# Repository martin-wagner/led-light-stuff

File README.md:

# led-light-stuff

various stuff to make led light
- circuit diagrams
- pcb images
- bom (not shure how accurate they are)
- image of hardware prototype

driver pins 2,3,4,5 - 9,10,11,12 - 17,18,19,20 do select microcontroller output color. solder only the one you want.

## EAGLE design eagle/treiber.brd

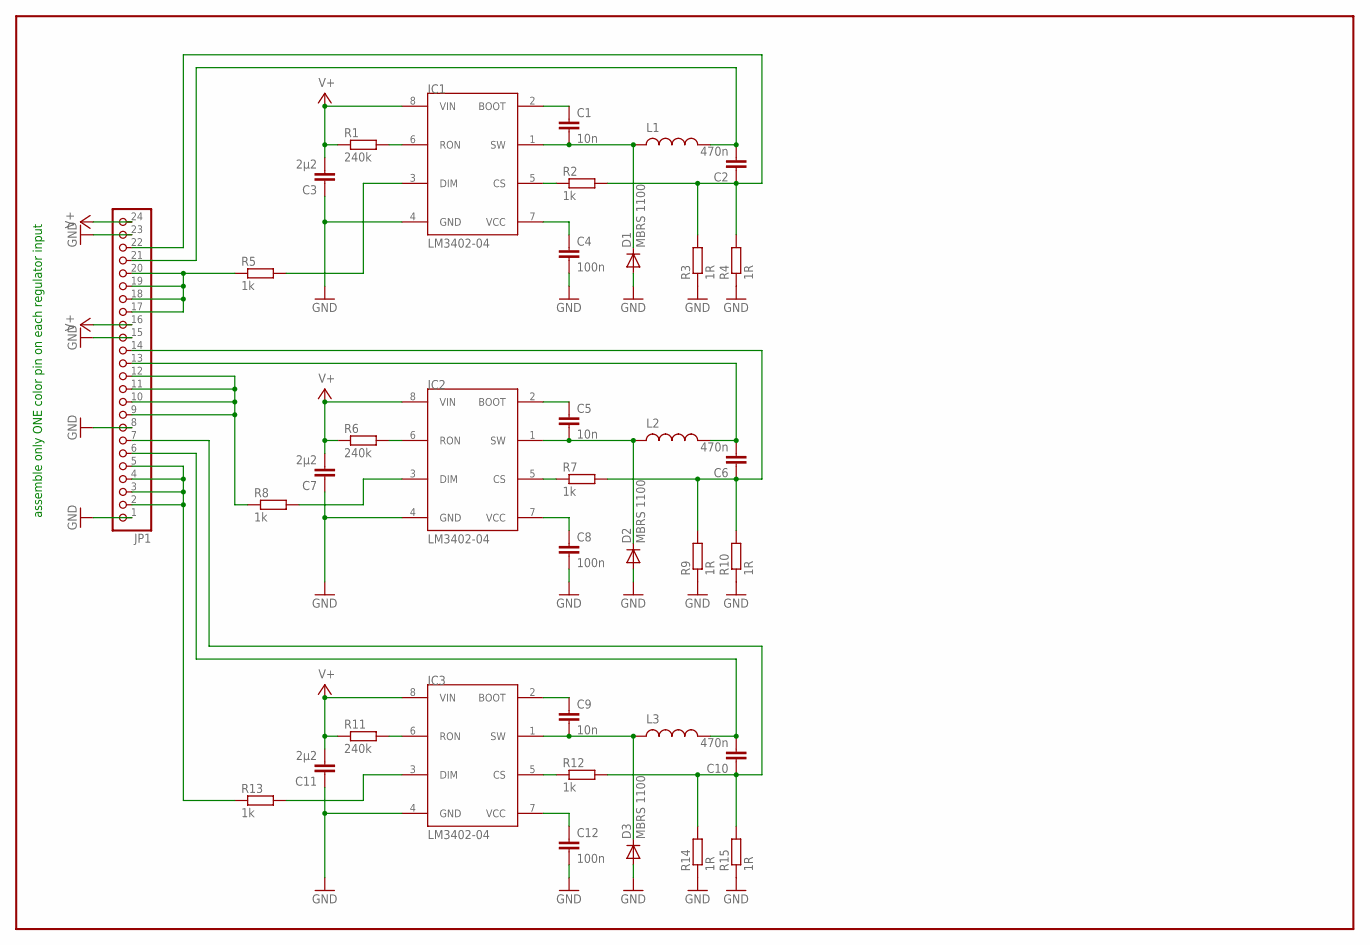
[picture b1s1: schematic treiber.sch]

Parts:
C1, C5, C9: 10n; C1206K
C2, C6, C10: 470n; C1206K
C3, C7, C11: 2µ2; C1206K
C4, C8, C12: 100n; C1206K
D1, D2, D3: MBRS 1100; DO214AA
IC1, IC2, IC3: LM3402-04; SOP08
JP1: PINHD-1X24_2.54-SMD-90°; 1X24SMD/90
L1, L2, L3: PIS4720; PIS
R1, R6, R11: 240k; R0805W
R2, R5, R7, R8, R12, R13: 1k; R1210W
R3, R4, R9, R10, R14, R15: 1R; R1210W

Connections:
GND: C3.1, C4.2, C7.1, C8.2, C11.1, C12.2, D1.A, D2.A, D3.A, IC1.4 (GND), IC2.4 (GND), IC3.4 (GND), JP1.1, JP1.8, JP1.15, JP1.23, R3.1, R4.1, R9.1, R10.1, R14.1, R15.1
unnamed: C4.1, IC1.7 (VCC)
unnamed: C1.1, IC1.2 (BOOT)
unnamed: C2.1, JP1.22, R2.2, R3.2, R4.2
unnamed: IC1.6 (RON), R1.2
unnamed: JP1.17, JP1.18, JP1.19, JP1.20, R5.1
unnamed: IC1.5 (CS), R2.1
unnamed: C1.2, D1.C, IC1.1 (SW), L1.P$2
unnamed: C2.2, JP1.21, L1.P$1
unnamed: IC1.3 (DIM), R5.2
unnamed: C8.1, IC2.7 (VCC)
unnamed: C5.1, IC2.2 (BOOT)
unnamed: IC2.6 (RON), R6.2
unnamed: JP1.9, JP1.10, JP1.11, JP1.12, R8.1
unnamed: IC2.5 (CS), R7.1
unnamed: C5.2, D2.C, IC2.1 (SW), L2.P$2
unnamed: C6.1, JP1.14, R7.2, R9.2, R10.2
unnamed: C6.2, JP1.13, L2.P$1
unnamed: IC2.3 (DIM), R8.2
unnamed: C12.1, IC3.7 (VCC)
unnamed: C9.1, IC3.2 (BOOT)
unnamed: IC3.6 (RON), R11.2
unnamed: JP1.2, JP1.3, JP1.4, JP1.5, R13.1
unnamed: IC3.5 (CS), R12.1
unnamed: C9.2, D3.C, IC3.1 (SW), L3.P$2
unnamed: C10.1, JP1.7, R12.2, R14.2, R15.2
unnamed: C10.2, JP1.6, L3.P$1
unnamed: IC3.3 (DIM), R13.2
V+: C3.2, C7.2, C11.2, IC1.8 (VIN), IC2.8 (VIN), IC3.8 (VIN), JP1.16, JP1.24, R1.1, R6.1, R11.1

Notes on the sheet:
assemble only ONE color pin on each regulator input

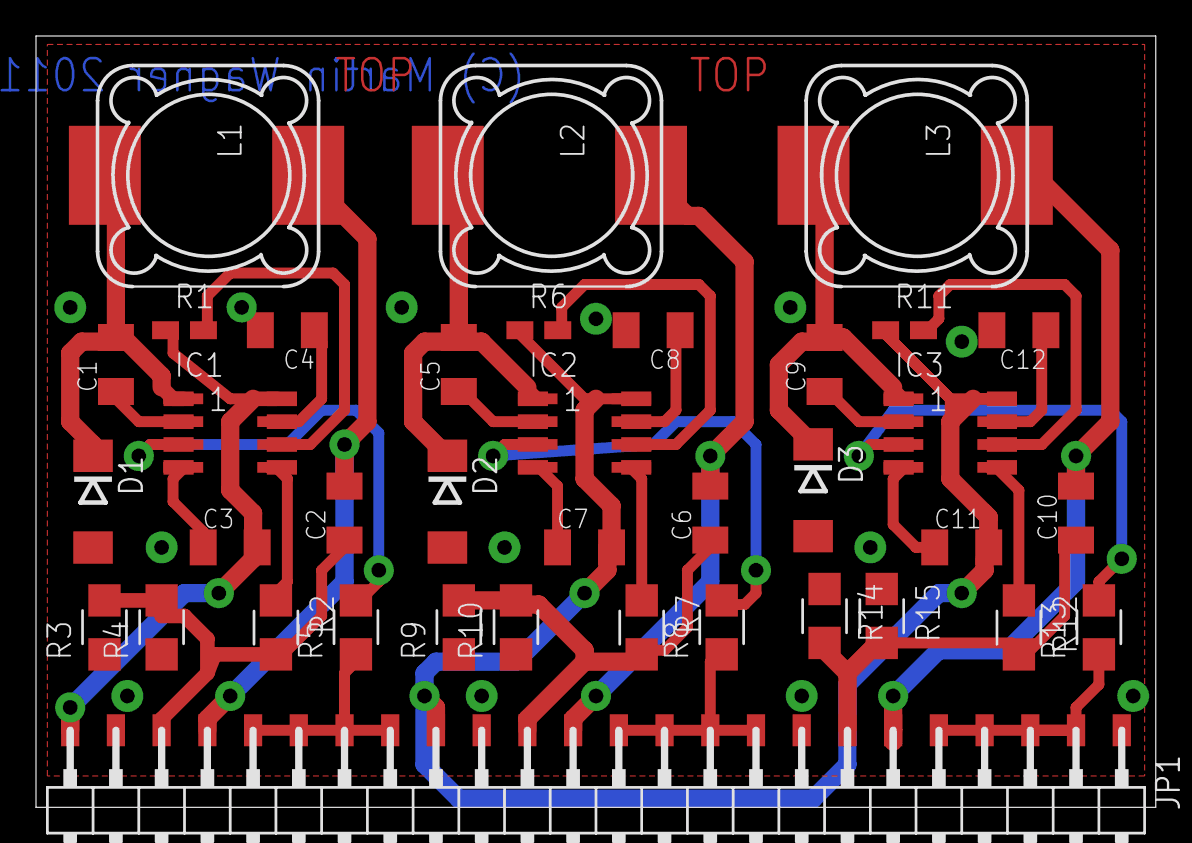
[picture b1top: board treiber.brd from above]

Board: 2 copper layers, 62.2 x 42.9 mm, 37 parts (0 on the bottom side), 29 nets.

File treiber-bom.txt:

Partlist

Exported from treiber.sch at 12/13/2015 03:47:06p

EAGLE Version 4.11 Copyright (c) 1988-2003 CadSoft

Part     Value          Device                  Package    Library   Sheet

C1       10n            C-EUC1206K              C1206K     rcl       1
C2       470n           C-EUC1206K              C1206K     rcl       1
C3       2µ2            C-EUC1206K              C1206K     rcl       1
C4       100n           C-EUC1206K              C1206K     rcl       1
C5       10n            C-EUC1206K              C1206K     rcl       1
C6       470n           C-EUC1206K              C1206K     rcl       1
C7       2µ2            C-EUC1206K              C1206K     rcl       1
C8       100n           C-EUC1206K              C1206K     rcl       1
C9       10n            C-EUC1206K              C1206K     rcl       1
C10      470n           C-EUC1206K              C1206K     rcl       1
C11      2µ2            C-EUC1206K              C1206K     rcl       1
C12      100n           C-EUC1206K              C1206K     rcl       1
D1       MBRS 1100      DIODE-                  DO214AA    diode     1
D2       MBRS 1100      DIODE-                  DO214AA    diode     1
D3       MBRS 1100      DIODE-                  DO214AA    diode     1
IC1      LM3402-04      LM3402-04               SOP08      Martin    1
IC2      LM3402-04      LM3402-04               SOP08      Martin    1
IC3      LM3402-04      LM3402-04               SOP08      Martin    1
JP1                     PINHD-1X24_2.54-SMD-90° 1X24SMD/90 pinhead-1 1
L1                      PIS4720                 PIS        Martin    1
L2                      PIS4720                 PIS        Martin    1
L3                      PIS4720                 PIS        Martin    1
R1       240k           R-EU_R0805W             R0805W     rcl       1
R2       1k             R-EU_R1210W             R1210W     rcl       1
R3       1R             R-EU_R1210W             R1210W     rcl       1
R4       1R             R-EU_R1210W             R1210W     rcl       1
R5       1k             R-EU_R1210W             R1210W     rcl       1
R6       240k           R-EU_R0805W             R0805W     rcl       1
R7       1k             R-EU_R1210W             R1210W     rcl       1
R8       1k             R-EU_R1210W             R1210W     rcl       1
R9       1R             R-EU_R1210W             R1210W     rcl       1
R10      1R             R-EU_R1210W             R1210W     rcl       1
R11      240k           R-EU_R0805W             R0805W     rcl       1
R12      1k             R-EU_R1210W             R1210W     rcl       1
R13      1k             R-EU_R1210W             R1210W     rcl       1
R14      1R             R-EU_R1210W             R1210W     rcl       1
R15      1R             R-EU_R1210W             R1210W     rcl       1

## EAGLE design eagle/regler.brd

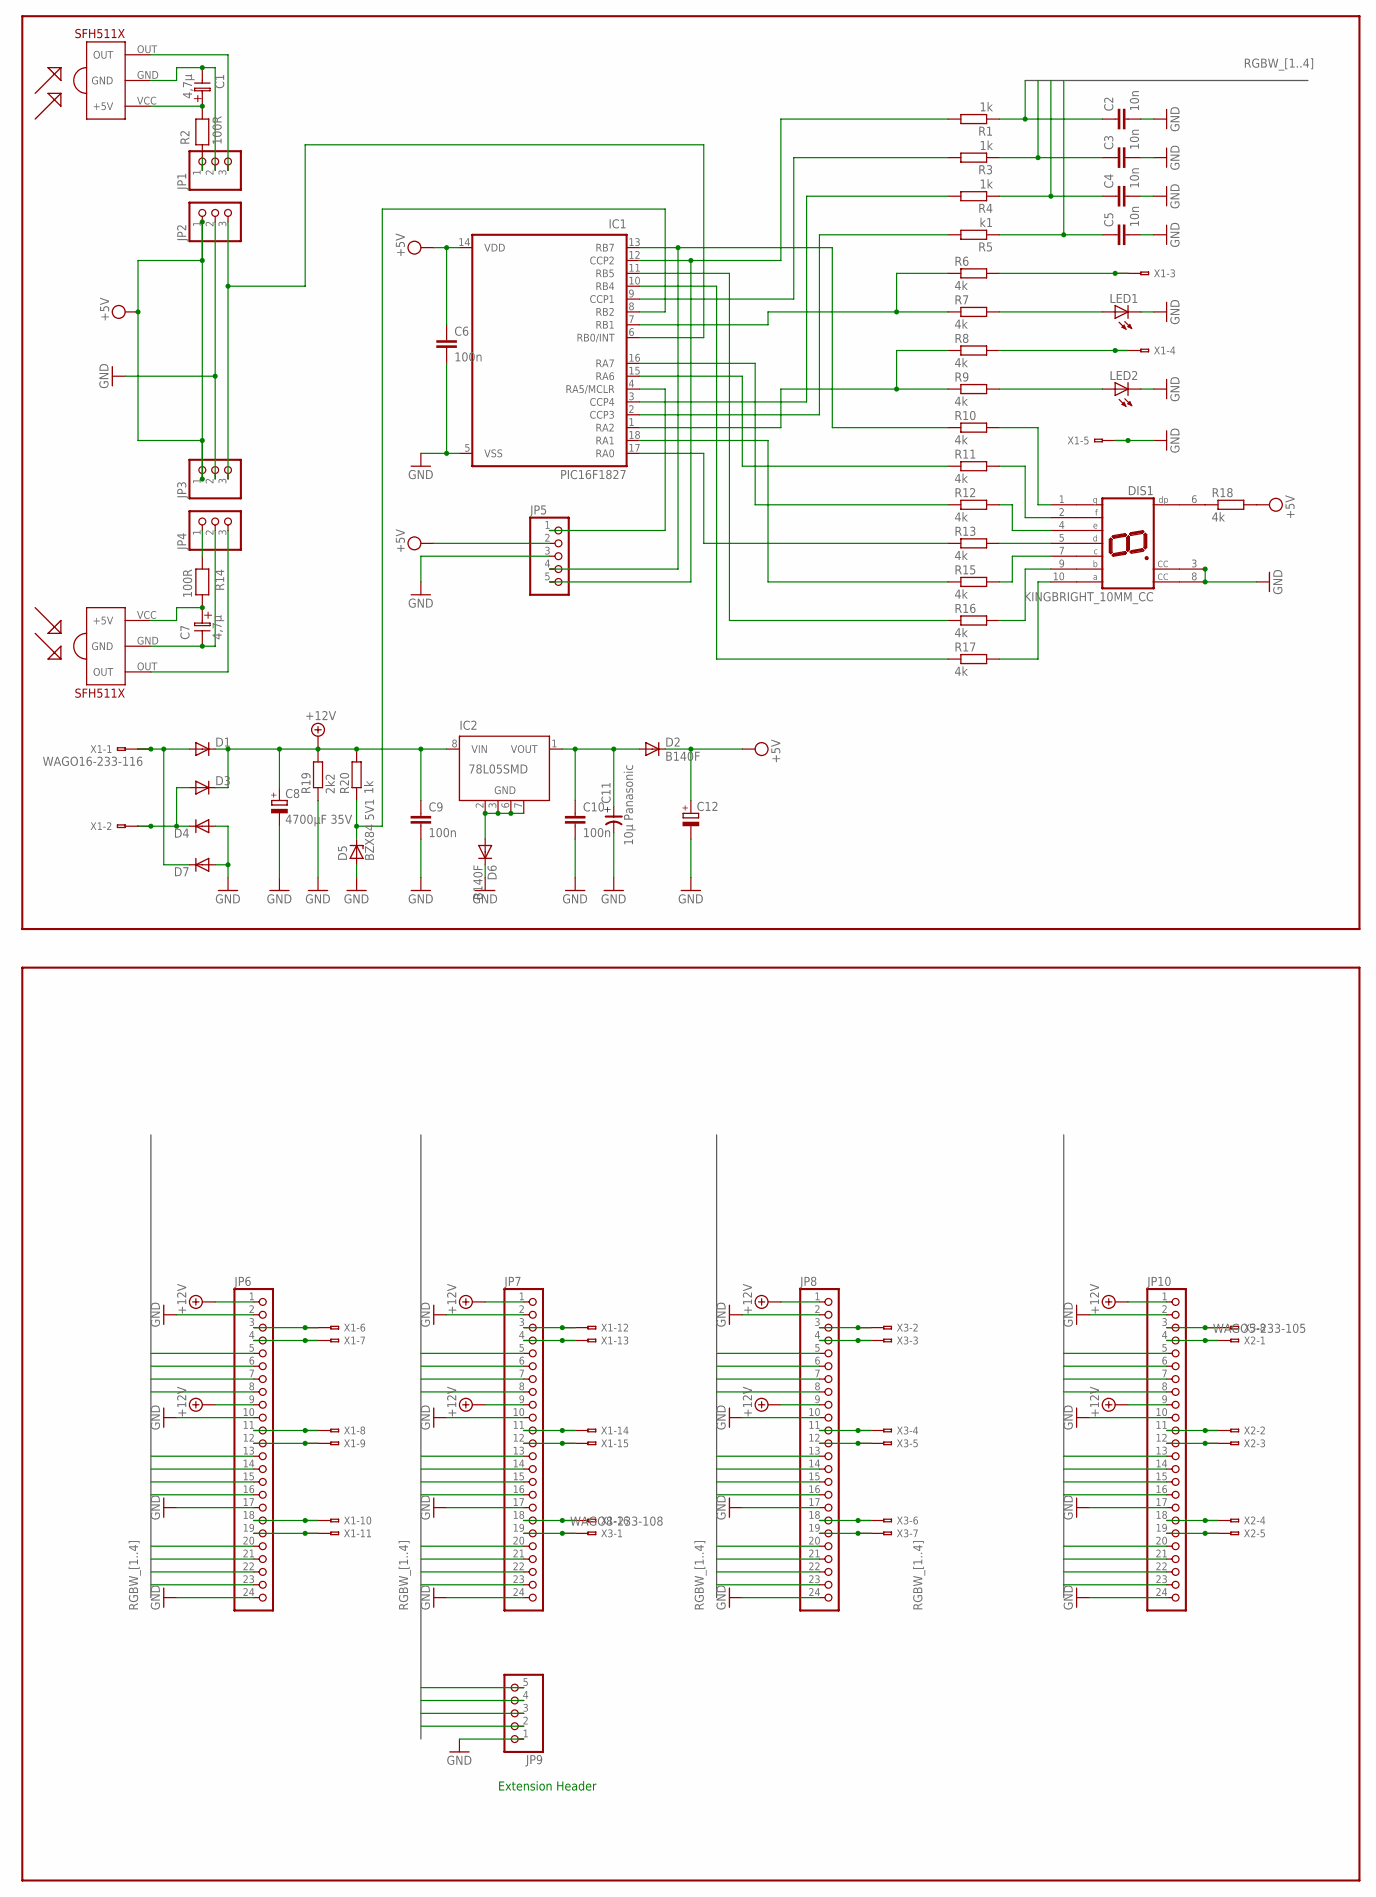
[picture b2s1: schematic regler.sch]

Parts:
C1, C7: 4,7µ; ES-2,5
C2, C3, C4, C5: 10n; C1206K
C6, C9, C10: 100n; C1206K
C8: 4700µF 35V; E7,5-18
C11: 10µ Panasonic; SV-B
C12: CPOL-EUE5-5; E5-5
D1, D3, D4, D7: DIODE-SMC; SMC
D2, D6: B140F; DO214AA
D5: BZX84 5V1; TO236
DIS1: KINGBRIGHT_10MM_CC; HDSP-E
IC1: PIC16F1827; SO-18W
IC2: 78L05SMD; SO08
IR-RECEIVERS1, IR-RECEIVERS2: SFH511XB; SFH5110
JP1, JP4: PINHD-1X3_2.54; 1X03
JP2, JP3: PINHD-1X3_2.54-SMD; 1X03SMD
JP5: PINHD-1X5_2.54-SMD; 1X05SMD
JP6, JP7, JP8, JP10: PINHD-1X24_2.54-SMD; 1X24SMD
JP9: PINHD-1X5_2.54-SMD-90°; 1X05SMD/90
LED1, LED2: LEDCHIPLED_1206; CHIPLED_1206
R1, R3, R4, R20: 1k; R1210W
R2, R14: 100R; R-10
R5: k1; R1210W
R6, R7, R8, R9, R10, R11, R12, R13, R15, R16, R17, R18: 4k; R0805W
R19: 2k2; R1210W
X1: WAGO16-233-116; 233-116
X2: WAGO5-233-105; 233-105
X3: WAGO8-233-108; 233-108

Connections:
+12V: C8.+, C9.1, D1.C, D3.C, IC2.8 (VIN), JP6.1, JP6.9, JP7.1, JP7.9, JP8.1, JP8.9, JP10.1, JP10.9, R19.2, R20.2
ABC: IC1.12 (CCP2), JP5.5, R1.2
DEF: IC1.9 (CCP1), R3.2
GHI: IC1.3 (CCP4), R4.2
GND: C1.2, C2.2, C3.2, C4.2, C5.2, C6.2, C7.2, C8.-, C9.2, C10.2, C11.-, C12.-, D4.A, D5.A, D6.C, D7.A, DIS1.3 (CC), DIS1.8 (CC), IC1.5 (VSS), IR-RECEIVERS1.GND, IR-RECEIVERS2.GND, JP1.2, JP2.2, JP3.2, JP4.2, JP5.3, JP6.2, JP6.10, JP6.17, JP6.24, JP7.2, JP7.10, JP7.17, JP7.24, JP8.2, JP8.10, JP8.17, JP8.24, JP9.1, JP10.2, JP10.10, JP10.17, JP10.24, LED1.C, LED2.C, R19.1, X1.A5 (A1), X1.B5 (B1)
JKL: IC1.2 (CCP3), R5.2
unnamed: D1.A, D7.C, X1.A1, X1.B1
unnamed: D3.A, D4.C, X1.A2 (A1), X1.B2 (B1)
unnamed: JP6.3, X1.A6 (A1), X1.B6 (B1)
unnamed: D6.A, IC2.2 (GND), IC2.3 (GND), IC2.6 (GND), IC2.7 (GND)
unnamed: C10.1, C11.+, D2.A, IC2.1 (VOUT)
unnamed: D5.C, IC1.8 (RB2), R20.1
unnamed: JP6.4, X1.A7 (A1), X1.B7 (B1)
unnamed: DIS1.6 (DP), R18.1
unnamed: IC1.17 (RA0), R13.1
unnamed: IC1.16 (RA7), R12.1
unnamed: IC1.15 (RA6), R11.1
unnamed: IC1.13 (RB7), JP5.4, R10.1
unnamed: IC1.10 (RB4), R17.1
unnamed: LED2.A, R9.2
unnamed: IC1.7 (RB1), R6.1, R7.1
unnamed: LED1.A, R7.2
unnamed: IC1.6 (RB0/INT), JP2.3, JP3.3
unnamed: R8.2, X1.A4 (A1), X1.B4 (B1)
unnamed: R6.2, X1.A3 (A1), X1.B3 (B1)
unnamed: C1.1, IR-RECEIVERS1.VCC (+5V), R2.2
unnamed: JP1.1, R2.1
unnamed: C7.1, IR-RECEIVERS2.VCC (+5V), R14.2
unnamed: JP4.1, R14.1
unnamed: DIS1.1 (G), R10.2
unnamed: DIS1.2 (F), R11.2
unnamed: DIS1.4 (E), R12.2
unnamed: DIS1.5 (D), R13.2
unnamed: DIS1.7 (C), R15.2
unnamed: DIS1.9 (B), R16.2
unnamed: DIS1.10 (A), R17.2
unnamed: JP10.3, X3.A8 (A1), X3.B8 (B1)
unnamed: JP6.11, X1.A8 (A1), X1.B8 (B1)
unnamed: JP6.12, X1.A9 (A1), X1.B9 (B1)
unnamed: JP6.18, X1.A10 (A1), X1.B10 (B1)
unnamed: JP6.19, X1.A11 (A1), X1.B11 (B1)
unnamed: JP7.3, X1.A12 (A1), X1.B12 (B1)
unnamed: JP7.4, X1.A13 (A1), X1.B13 (B1)
unnamed: JP7.11, X1.A14 (A1), X1.B14 (B1)
unnamed: JP7.12, X1.A15 (A1), X1.B15 (B1)
unnamed: JP7.18, X1.A16 (A1), X1.B16 (B1)
unnamed: JP7.19, X3.A1, X3.B1
unnamed: JP8.3, X3.A2 (A1), X3.B2 (B1)
unnamed: JP8.4, X3.A3 (A1), X3.B3 (B1)
unnamed: JP8.11, X3.A4 (A1), X3.B4 (B1)
unnamed: JP8.12, X3.A5 (A1), X3.B5 (B1)
unnamed: JP8.18, X3.A6 (A1), X3.B6 (B1)
unnamed: JP8.19, X3.A7 (A1), X3.B7 (B1)
unnamed: IC1.11 (RB5), R16.1
unnamed: JP10.4, X2.A1, X2.B1
unnamed: IC1.18 (RA1), R15.1
unnamed: JP10.11, X2.A2 (A1), X2.B2 (B1)
unnamed: IC1.4 (RA5/MCLR), JP5.1
unnamed: JP10.12, X2.A3 (A1), X2.B3 (B1)
unnamed: JP10.18, X2.A4 (A1), X2.B4 (B1)
unnamed: JP10.19, X2.A5 (A1), X2.B5 (B1)
unnamed: IC1.1 (RA2), R8.1, R9.1
OUT: IR-RECEIVERS1.OUT, IR-RECEIVERS2.OUT, JP1.3, JP4.3
RGBW_1: C2.1, JP6.8, JP6.16, JP6.23, JP7.8, JP7.16, JP7.23, JP8.8, JP8.16, JP8.23, JP9.5, JP10.8, JP10.16, JP10.23, R1.1
RGBW_2: C5.1, JP6.7, JP6.15, JP6.22, JP7.7, JP7.15, JP7.22, JP8.7, JP8.15, JP8.22, JP9.4, JP10.7, JP10.15, JP10.22, R5.1
RGBW_3: C4.1, JP6.6, JP6.14, JP6.21, JP7.6, JP7.14, JP7.21, JP8.6, JP8.14, JP8.21, JP9.3, JP10.14, JP10.21, R4.1
RGBW_4: C3.1, JP6.5, JP6.13, JP6.20, JP7.5, JP7.13, JP7.20, JP8.5, JP8.13, JP8.20, JP9.2, JP10.5, JP10.13, JP10.20, R3.1
VDD: C6.1, C12.+, D2.C, IC1.14 (VDD), JP2.1, JP3.1, JP5.2, R18.2

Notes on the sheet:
Extension Header

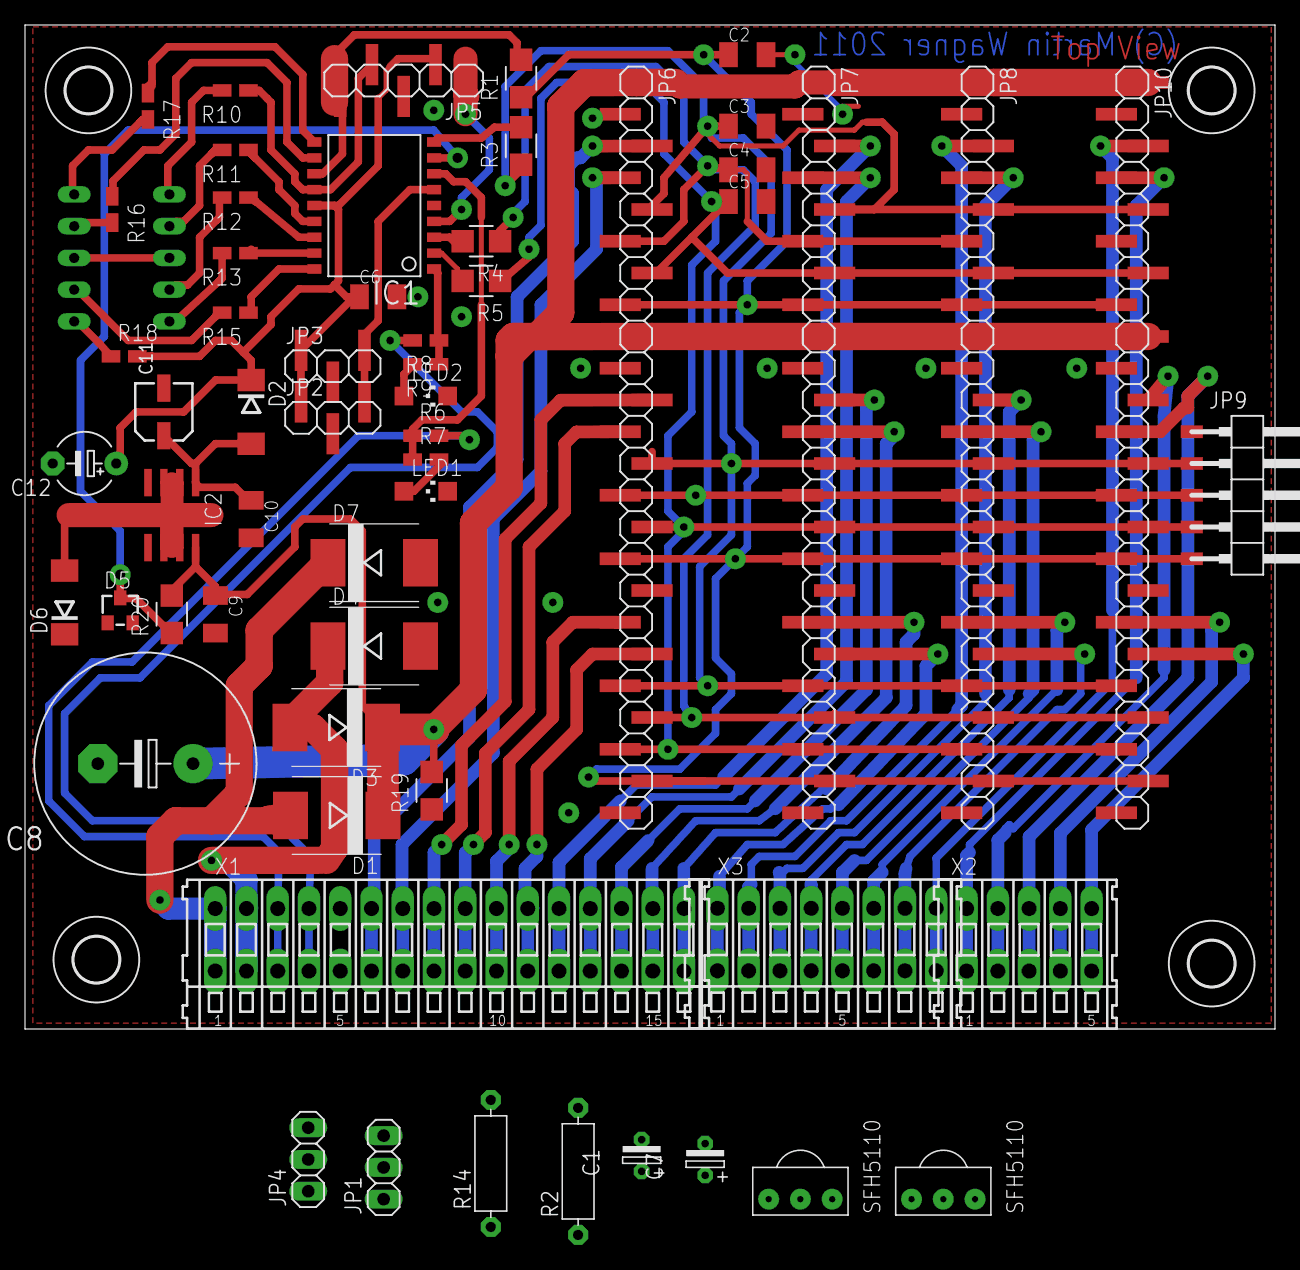
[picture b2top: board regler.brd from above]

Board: 2 copper layers, 100.0 x 80.3 mm, 63 parts (1 on the bottom side), 68 nets.

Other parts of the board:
U$1, U$2, U$3, U$4: 3,6

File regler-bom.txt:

Partlist

Exported from regler.sch at 12/13/2015 03:46:54p

EAGLE Version 4.11 Copyright (c) 1988-2003 CadSoft

Part          Value              Device                       Package      Library    Sheet

C1            4,7µ               ELC-2,5                      ES-2,5       discrete   1
C2            10n                C-EUC1206K                   C1206K       rcl        1
C3            10n                C-EUC1206K                   C1206K       rcl        1
C4            10n                C-EUC1206K                   C1206K       rcl        1
C5            10n                C-EUC1206K                   C1206K       rcl        1
C6            100n               C-EUC1206K                   C1206K       rcl        1
C7            4,7µ               ELC-2,5                      ES-2,5       discrete   1
C8            4700µF 35V         CPOL-EUE7.5-18               E7,5-18      rcl        1
C9            100n               C-EUC1206K                   C1206K       rcl        1
C10           100n               C-EUC1206K                   C1206K       rcl        1
C11           10µ Panasonic      CP-SV-B                      SV-B         cap-master 1
C12                              CPOL-EUE5-5                  E5-5         rcl        1
D1                               DIODE-SMC                    SMC          diode      1
D2            B140F              DIODE-                       DO214AA      diode      1
D3                               DIODE-SMC                    SMC          diode      1
D4                               DIODE-SMC                    SMC          diode      1
D5            BZX84 5V1          BZX84CSMD                    TO236        diode      1
D6            B140F              DIODE-                       DO214AA      diode      1
D7                               DIODE-SMC                    SMC          diode      1
DIS1          KINGBRIGHT_10MM_CC KINGBRIGHT_10MM_CC           HDSP-E       Martin     1
IC1           PIC16F1827         PIC16F1827_RGB_CONTROLLER7SO SO-18W       Martin     1
IC2           78L05SMD           78L05SMD                     SO08         linear     1
IR-RECEIVERS1                    SFH511XB                     SFH5110      sfh511x    1
IR-RECEIVERS2                    SFH511XB                     SFH5110      sfh511x    1
JP1                              PINHD-1X3_2.54               1X03         pinhead-1  1
JP2                              PINHD-1X3_2.54-SMD           1X03SMD      pinhead-1  1
JP3                              PINHD-1X3_2.54-SMD           1X03SMD      pinhead-1  1
JP4                              PINHD-1X3_2.54               1X03         pinhead-1  1
JP5                              PINHD-1X5_2.54-SMD           1X05SMD      pinhead-1  1
JP6                              PINHD-1X24_2.54-SMD          1X24SMD      pinhead-1  1
JP7                              PINHD-1X24_2.54-SMD          1X24SMD      pinhead-1  1
JP8                              PINHD-1X24_2.54-SMD          1X24SMD      pinhead-1  1
JP9                              PINHD-1X5_2.54-SMD-90°       1X05SMD/90   pinhead-1  1
JP10                             PINHD-1X24_2.54-SMD          1X24SMD      pinhead-1  1
LED1                             LEDCHIPLED_1206              CHIPLED_1206 led        1
LED2                             LEDCHIPLED_1206              CHIPLED_1206 led        1
R1            1k                 R-EU_R1210W                  R1210W       rcl        1
R2            100R               RESEU-10                     R-10         discrete   1
R3            1k                 R-EU_R1210W                  R1210W       rcl        1
R4            1k                 R-EU_R1210W                  R1210W       rcl        1
R5            k1                 R-EU_R1210W                  R1210W       rcl        1
R6            4k                 R-EU_R0805W                  R0805W       rcl        1
R7            4k                 R-EU_R0805W                  R0805W       rcl        1
R8            4k                 R-EU_R0805W                  R0805W       rcl        1
R9            4k                 R-EU_R0805W                  R0805W       rcl        1
R10           4k                 R-EU_R0805W                  R0805W       rcl        1
R11           4k                 R-EU_R0805W                  R0805W       rcl        1
R12           4k                 R-EU_R0805W                  R0805W       rcl        1
R13           4k                 R-EU_R0805W                  R0805W       rcl        1
R14           100R               RESEU-10                     R-10         discrete   1
R15           4k                 R-EU_R0805W                  R0805W       rcl        1
R16           4k                 R-EU_R0805W                  R0805W       rcl        1
R17           4k                 R-EU_R0805W                  R0805W       rcl        1
R18           4k                 R-EU_R0805W                  R0805W       rcl        1
R19           2k2                R-EU_R1210W                  R1210W       rcl        1
R20           1k                 R-EU_R1210W                  R1210W       rcl        1
X1            WAGO16-233-116     WAGO16-233-116               233-116      con-wago   1
X2            WAGO5-233-105      WAGO5-233-105                233-105      con-wago   1
X3            WAGO8-233-108      WAGO8-233-108                233-108      con-wago   1

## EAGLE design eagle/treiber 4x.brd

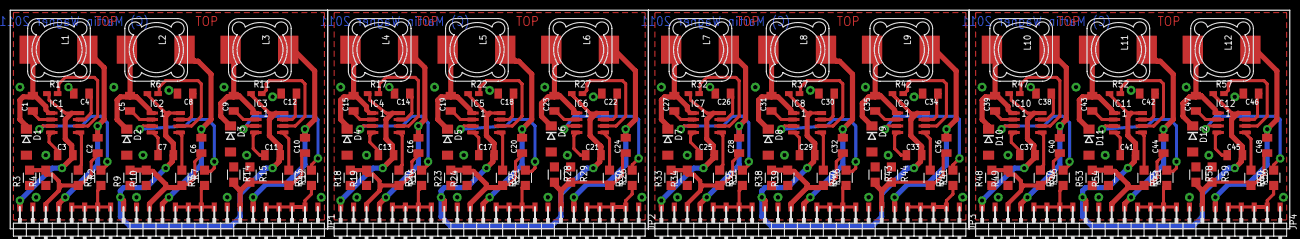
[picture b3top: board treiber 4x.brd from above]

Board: 2 copper layers, 250.8 x 42.9 mm, 148 parts (0 on the bottom side), 116 nets.

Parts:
C1, C5, C9, C15, C19, C23, C27, C31, C35, C39, C43, C47: 10n; C1206K
C2, C6, C10, C16, C20, C24, C28, C32, C36, C40, C44, C48: 470n; C1206K
C3, C7, C11, C13, C17, C21, C25, C29, C33, C37, C41, C45: 2µ2; C1206K
C4, C8, C12, C14, C18, C22, C26, C30, C34, C38, C42, C46: 100n; C1206K
D1, D2, D3, D4, D5, D6, D7, D8, D9, D10, D11, D12: MBRS 1100; DO214AA
IC1, IC2, IC3, IC4, IC5, IC6, IC7, IC8, IC9, IC10, IC11, IC12: LM3402-04; SOP08
JP1, JP2, JP3, JP4: 1X24SMD/90
L1, L2, L3, L4, L5, L6, L7, L8, L9, L10, L11, L12: PIS
R1, R6, R11, R17, R22, R27, R32, R37, R42, R47, R52, R57: 240k; R0805W
R2, R5, R7, R8, R12, R13, R16, R20, R21, R25, R26, R30, R31, R35, R36, R40, R41, R45, R46, R50, R51, R55, R56, R60: 1k; R1210W
R3, R4, R9, R10, R14, R15, R18, R19, R23, R24, R28, R29, R33, R34, R38, R39, R43, R44, R48, R49, R53, R54, R58, R59: 1R; R1210W

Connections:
GND: C3.1, C4.2, C7.1, C8.2, C11.1, C12.2, D1.A, D2.A, D3.A, IC1.4, IC2.4, IC3.4, JP1.1, JP1.8, JP1.15, JP1.23, R3.1, R4.1, R9.1, R10.1, R14.1, R15.1
GND1: C13.1, C14.2, C17.1, C18.2, C21.1, C22.2, D4.A, D5.A, D6.A, IC4.4, IC5.4, IC6.4, JP2.1, JP2.8, JP2.15, JP2.23, R18.1, R19.1, R23.1, R24.1, R28.1, R29.1
GND2: C25.1, C26.2, C29.1, C30.2, C33.1, C34.2, D7.A, D8.A, D9.A, IC7.4, IC8.4, IC9.4, JP3.1, JP3.8, JP3.15, JP3.23, R33.1, R34.1, R38.1, R39.1, R43.1, R44.1
GND3: C37.1, C38.2, C41.1, C42.2, C45.1, C46.2, D10.A, D11.A, D12.A, IC10.4, IC11.4, IC12.4, JP4.1, JP4.8, JP4.15, JP4.23, R48.1, R49.1, R53.1, R54.1, R58.1, R59.1
unnamed: C14.1, IC4.7
unnamed: C15.1, IC4.2
unnamed: IC4.6, R17.2
unnamed: JP2.17, JP2.18, JP2.19, JP2.20, R20.1
unnamed: IC4.5, R16.1
unnamed: C15.2, D4.C, IC4.1, L4.P$2
unnamed: C16.1, JP2.22, R16.2, R18.2, R19.2
unnamed: C16.2, JP2.21, L4.P$1
unnamed: IC4.3, R20.2
unnamed: C18.1, IC5.7
unnamed: C19.1, IC5.2
unnamed: IC5.6, R22.2
unnamed: JP2.9, JP2.10, JP2.11, JP2.12, R25.1
unnamed: IC5.5, R21.1
unnamed: C19.2, D5.C, IC5.1, L5.P$2
unnamed: C20.1, JP2.14, R21.2, R23.2, R24.2
unnamed: C20.2, JP2.13, L5.P$1
unnamed: IC5.3, R25.2
unnamed: C22.1, IC6.7
unnamed: C23.1, IC6.2
unnamed: IC6.6, R27.2
unnamed: IC6.5, R26.1
unnamed: C23.2, D6.C, IC6.1, L6.P$2
unnamed: C24.1, JP2.7, R26.2, R28.2, R29.2
unnamed: C24.2, JP2.6, L6.P$1
unnamed: IC6.3, R30.2
unnamed: JP2.2, JP2.3, JP2.4, JP2.5, R30.1
unnamed: C26.1, IC7.7
unnamed: C27.1, IC7.2
unnamed: IC7.6, R32.2
unnamed: JP3.17, JP3.18, JP3.19, JP3.20, R35.1
unnamed: IC7.5, R31.1
unnamed: C27.2, D7.C, IC7.1, L7.P$2
unnamed: C28.1, JP3.22, R31.2, R33.2, R34.2
unnamed: C28.2, JP3.21, L7.P$1
unnamed: IC7.3, R35.2
unnamed: C30.1, IC8.7
unnamed: C31.1, IC8.2
unnamed: IC8.6, R37.2
unnamed: JP3.9, JP3.10, JP3.11, JP3.12, R40.1
unnamed: IC8.5, R36.1
unnamed: C31.2, D8.C, IC8.1, L8.P$2
unnamed: C32.1, JP3.14, R36.2, R38.2, R39.2
unnamed: C32.2, JP3.13, L8.P$1
unnamed: IC8.3, R40.2
unnamed: C34.1, IC9.7
unnamed: C35.1, IC9.2
unnamed: C4.1, IC1.7
unnamed: C1.1, IC1.2
unnamed: C2.1, JP1.22, R2.2, R3.2, R4.2
unnamed: IC1.6, R1.2
unnamed: IC9.6, R42.2
unnamed: JP1.17, JP1.18, JP1.19, JP1.20, R5.1
unnamed: IC9.5, R41.1
unnamed: C35.2, D9.C, IC9.1, L9.P$2
unnamed: C36.1, JP3.7, R41.2, R43.2, R44.2
unnamed: IC1.5, R2.1
unnamed: C36.2, JP3.6, L9.P$1
unnamed: IC9.3, R45.2
unnamed: JP3.2, JP3.3, JP3.4, JP3.5, R45.1
unnamed: C38.1, IC10.7
unnamed: C1.2, D1.C, IC1.1, L1.P$2
unnamed: C2.2, JP1.21, L1.P$1
unnamed: IC1.3, R5.2
unnamed: C8.1, IC2.7
unnamed: C5.1, IC2.2
unnamed: IC2.6, R6.2
unnamed: JP1.9, JP1.10, JP1.11, JP1.12, R8.1
unnamed: IC2.5, R7.1
unnamed: C5.2, D2.C, IC2.1, L2.P$2
unnamed: C6.1, JP1.14, R7.2, R9.2, R10.2
unnamed: C6.2, JP1.13, L2.P$1
unnamed: IC2.3, R8.2
unnamed: C12.1, IC3.7
unnamed: C9.1, IC3.2
unnamed: IC3.6, R11.2
unnamed: JP1.2, JP1.3, JP1.4, JP1.5, R13.1
unnamed: IC3.5, R12.1
unnamed: C9.2, D3.C, IC3.1, L3.P$2
unnamed: C10.1, JP1.7, R12.2, R14.2, R15.2
unnamed: C10.2, JP1.6, L3.P$1
unnamed: IC3.3, R13.2
unnamed: C39.1, IC10.2
unnamed: IC10.6, R47.2
unnamed: JP4.17, JP4.18, JP4.19, JP4.20, R50.1
unnamed: IC10.5, R46.1
unnamed: C39.2, D10.C, IC10.1, L10.P$2
unnamed: C40.1, JP4.22, R46.2, R48.2, R49.2
unnamed: C40.2, JP4.21, L10.P$1
unnamed: IC10.3, R50.2
unnamed: C42.1, IC11.7
unnamed: C43.1, IC11.2
unnamed: IC11.6, R52.2
unnamed: JP4.9, JP4.10, JP4.11, JP4.12, R55.1
unnamed: IC11.5, R51.1
unnamed: C43.2, D11.C, IC11.1, L11.P$2
unnamed: C44.1, JP4.14, R51.2, R53.2, R54.2
unnamed: C44.2, JP4.13, L11.P$1
unnamed: IC11.3, R55.2
unnamed: C46.1, IC12.7
unnamed: C47.1, IC12.2
unnamed: IC12.6, R57.2
unnamed: IC12.5, R56.1
unnamed: C47.2, D12.C, IC12.1, L12.P$2
unnamed: C48.1, JP4.7, R56.2, R58.2, R59.2
unnamed: C48.2, JP4.6, L12.P$1
unnamed: IC12.3, R60.2
unnamed: JP4.2, JP4.3, JP4.4, JP4.5, R60.1
V+: C3.2, C7.2, C11.2, IC1.8, IC2.8, IC3.8, JP1.16, JP1.24, R1.1, R6.1, R11.1
V+1: C13.2, C17.2, C21.2, IC4.8, IC5.8, IC6.8, JP2.16, JP2.24, R17.1, R22.1, R27.1
V+2: C25.2, C29.2, C33.2, IC7.8, IC8.8, IC9.8, JP3.16, JP3.24, R32.1, R37.1, R42.1
V+3: C37.2, C41.2, C45.2, IC10.8, IC11.8, IC12.8, JP4.16, JP4.24, R47.1, R52.1, R57.1

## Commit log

2015-12-13 New: add various stuff
2015-12-13 New: converted eagle files to recent free version
